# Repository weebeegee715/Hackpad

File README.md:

# AJ'S Awesome Hackpad

### Inspiration

I really wanted to create something I could use for shortcuts while drawing in Clip Studio Paint!

### Challenges

Wiring the PCB to work and removing right angles was hard, but learning Fusion was harder.... Fusion oml...

### Specifications

BOM: 
- 6x Cherry MX Switches
- 1x XIAO RP2040
- 6x Blank DSA Keycaps
- 6x M3x16 Bolt
- 6x M3 Heatset
- 1x 0.91 inch OLED 

Others:
- KMK Firmware
- Top Case.stl 
- Bottom Case.stl

Schematic            |  PCB         |   Case
:-------------------------:|:-------------------------:|:-------------------------:|
  
  |  
  |

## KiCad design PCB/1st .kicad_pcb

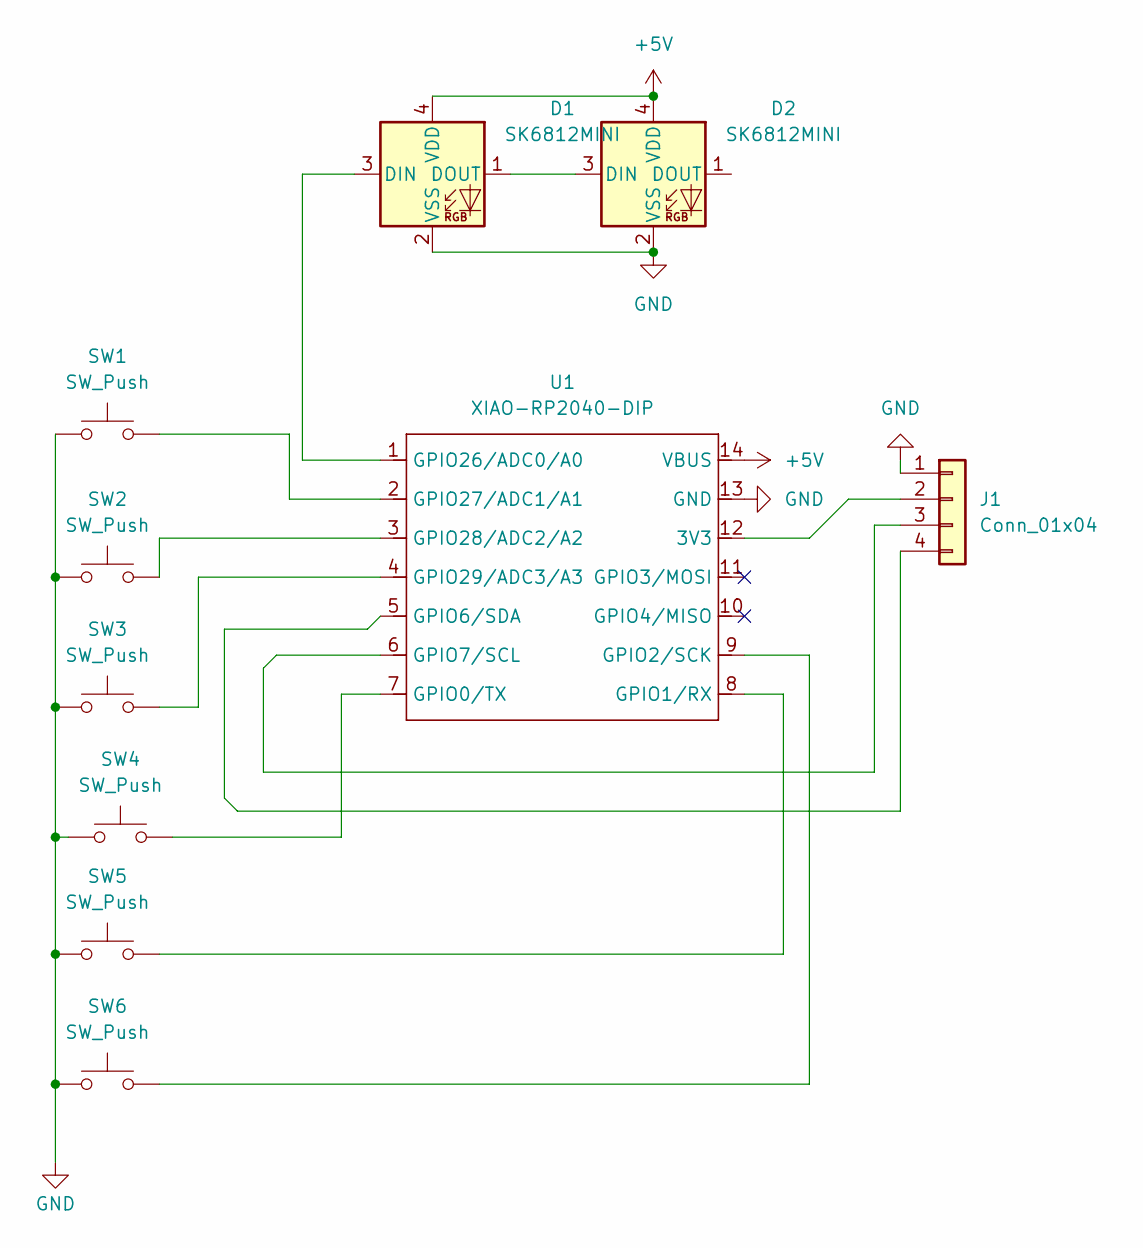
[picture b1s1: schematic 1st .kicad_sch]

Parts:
D1, D2: SK6812MINI; LED_SK6812MINI_PLCC4_3.5x3.5mm_P1.75mm
J1: Conn_01x04; SSD1306-0.91-OLED-4pin-128x32
SW1, SW2, SW3, SW4, SW5, SW6: SW_Push; SW_Cherry_MX_1.00u_PCB
U1: XIAO-RP2040-DIP

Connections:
+5V: D1.4 (VDD), D2.4 (VDD), U1.14 (VBUS)
GND: D1.2 (VSS), D2.2 (VSS), J1.1, SW1.1, SW2.1, SW3.1, SW4.1, SW5.1, SW6.1, U1.13 (GND)
unnamed: D1.3 (DIN), U1.1 (GPIO26/ADC0/A0)
unnamed: D1.1 (DOUT), D2.3 (DIN)
unnamed: J1.2, U1.12 (3V3)
unnamed: J1.3, U1.6 (GPIO7/SCL)
unnamed: J1.4, U1.5 (GPIO6/SDA)
unnamed: SW4.2, U1.7 (GPIO0/TX)
unnamed: SW5.2, U1.8 (GPIO1/RX)
unnamed: SW6.2, U1.9 (GPIO2/SCK)
unnamed: SW1.2, U1.2 (GPIO27/ADC1/A1)
unnamed: SW2.2, U1.3 (GPIO28/ADC2/A2)
unnamed: SW3.2, U1.4 (GPIO29/ADC3/A3)

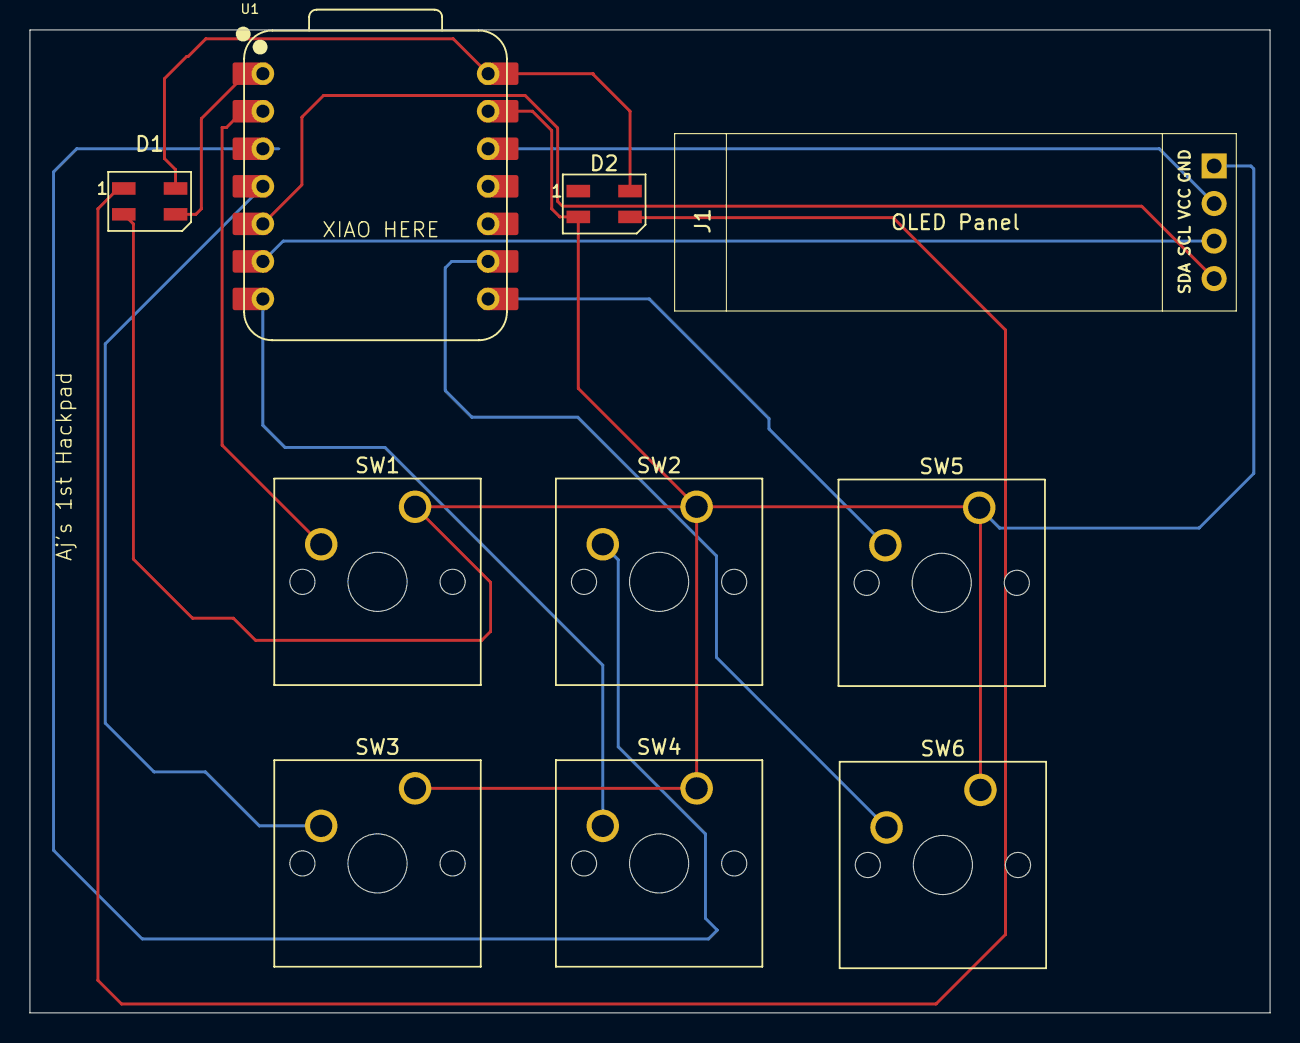
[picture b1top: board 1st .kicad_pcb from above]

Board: 2 copper layers, 83.9 x 66.5 mm, 10 parts (0 on the bottom side), 13 nets.

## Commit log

2026-01-04 my first commit into hackpad repository
2026-01-04 Add README
2026-01-04 Basic Firmware
2026-01-04 Enhance README with new images and alt text
    Updated images and added alt attributes for accessibility.
